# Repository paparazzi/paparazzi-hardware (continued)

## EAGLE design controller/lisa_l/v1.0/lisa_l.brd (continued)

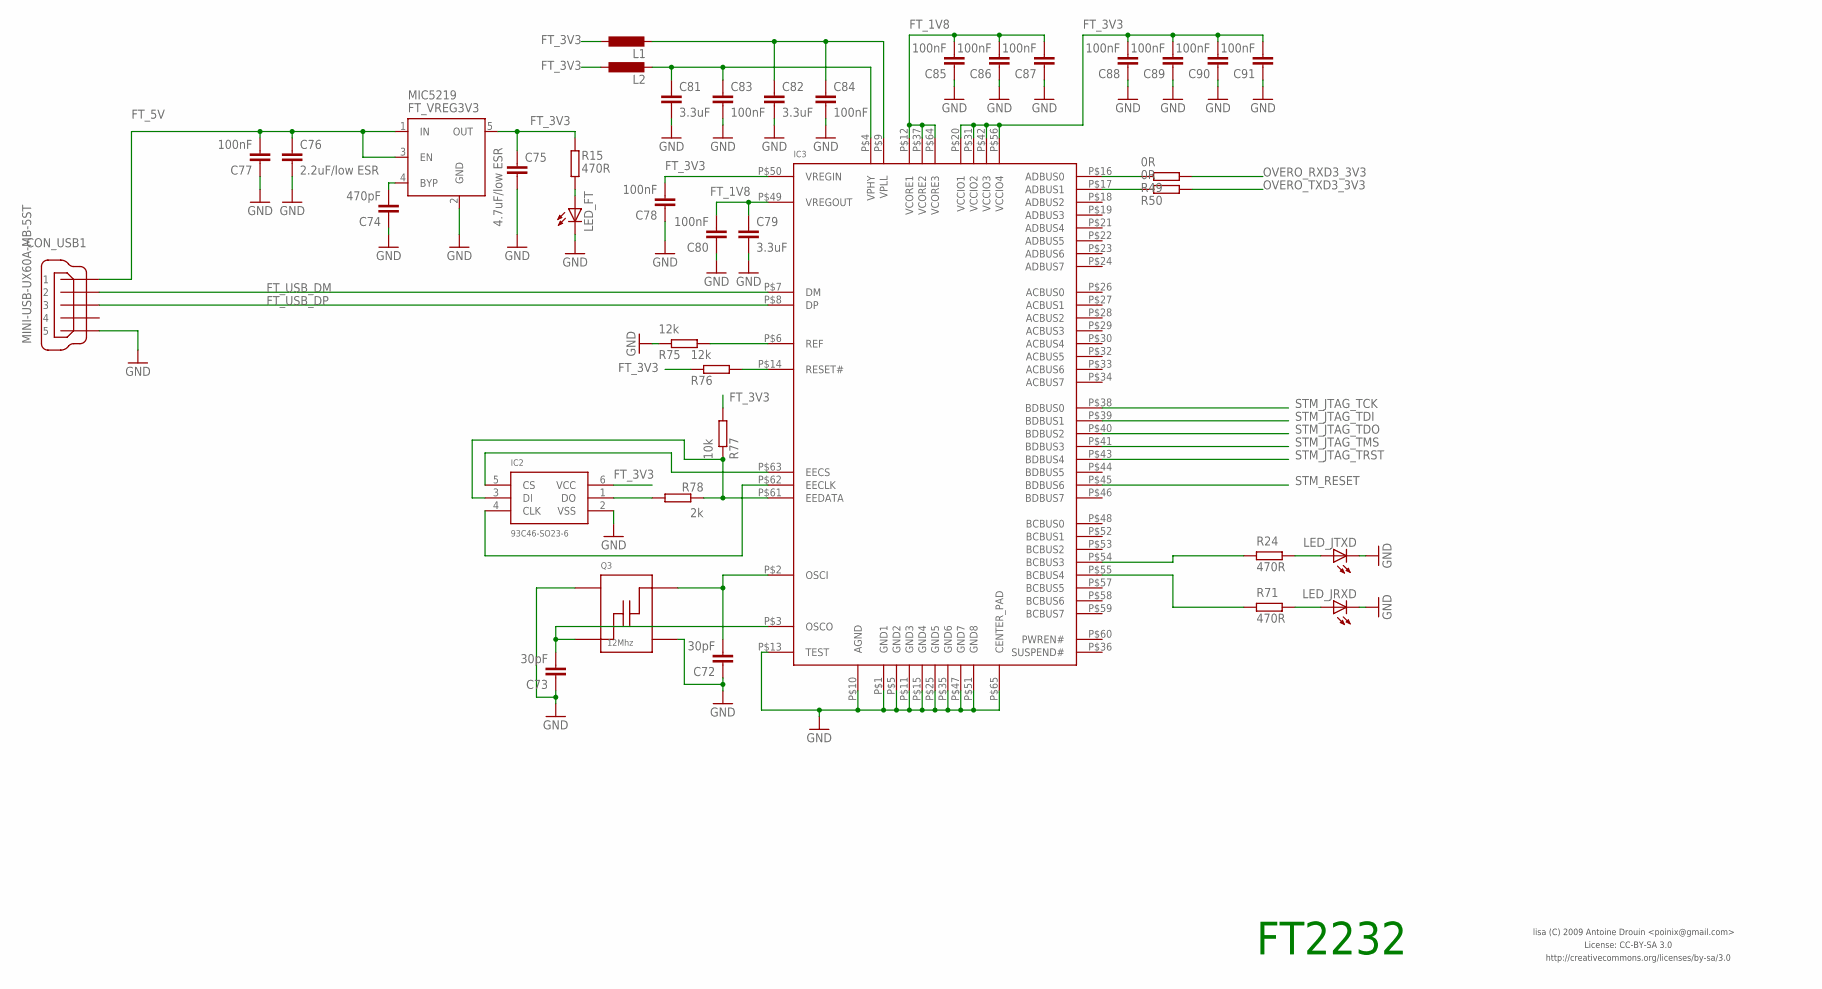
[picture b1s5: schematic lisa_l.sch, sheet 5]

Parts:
C72, C73: 30pF; 0603-CAP
C74: 470pF; 0603-CAP
C75: 4.7uF/low ESR; 0603-CAP
C76: 2.2uF/low ESR; 0603-CAP
C77, C78, C80, C83, C84, C85, C86, C87, C88, C89, C90, C91: 100nF; 0603-CAP
C79, C81, C82: 3.3uF; 0603-CAP
CON_USB1: MINI-USB-UX60A-MB-5ST; UX60A-MB-5ST
FT_VREG3V3: MIC5219; SOT23-5
IC2: 93C46-SO23-6; SO23-6
IC3: FT2232HQ; QFN64
L1, L2: INDUCTOR-0603; 0603-IND
LED_FT: LED-0603; 0603-LED
LED_JRXD: LED-0603; 0603-LED
LED_JTXD: LED-0603; 0603-LED
Q3: 12Mhz; ABM8
R15, R24, R71: 470R; 0603-RES
R49, R50: 0R; 0603-RES
R75, R76: 12k; 0603-RES
R77: 10k; 0603-RES
R78: 2k; 0603-RES

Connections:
FT_1V8: C79.P$1 (1), C80.P$2 (2), C85.P$2 (2), C86.P$2 (2), C87.P$2 (2), IC3.P$12 (VCORE1), IC3.P$37 (VCORE2), IC3.P$49 (VREGOUT), IC3.P$64 (VCORE3)
FT_3V3: C75.P$1 (1), C78.P$2 (2), C88.P$2 (2), C89.P$2 (2), C90.P$2 (2), C91.P$2 (2), FT_VREG3V3.5 (OUT), IC2.6 (VCC), IC3.P$20 (VCCIO1), IC3.P$31 (VCCIO2), IC3.P$42 (VCCIO3), IC3.P$50 (VREGIN), IC3.P$56 (VCCIO4), L1.P$1 (1), L2.P$1 (1), R15.P$2 (2), R76.P$1 (1), R77.P$2 (2)
FT_5V: C76.P$1 (1), C77.P$2 (2), CON_USB1.1, FT_VREG3V3.1 (IN), FT_VREG3V3.3 (EN)
FT_USB_DM: CON_USB1.2, IC3.P$7 (DM)
FT_USB_DP: CON_USB1.3, IC3.P$8 (DP)
GND: C72.P$1 (1), C73.P$1 (1), C74.P$1 (1), C75.P$2 (2), C76.P$2 (2), C77.P$1 (1), C78.P$1 (1), C79.P$2 (2), C80.P$1 (1), C81.P$2 (2), C82.P$2 (2), C83.P$2 (2), C84.P$2 (2), C85.P$1 (1), C86.P$1 (1), C87.P$1 (1), C88.P$1 (1), C89.P$1 (1), C90.P$1 (1), C91.P$1 (1), CON_USB1.5, FT_VREG3V3.2 (GND), IC2.2 (VSS), IC3.P$1 (GND1), IC3.P$5 (GND2), IC3.P$10 (AGND), IC3.P$11 (GND3), IC3.P$13 (TEST), IC3.P$15 (GND4), IC3.P$25 (GND5), IC3.P$35 (GND6), IC3.P$47 (GND7), IC3.P$51 (GND8), IC3.P$65 (CENTER_PAD), LED_FT.C, LED_JRXD.C, LED_JTXD.C, Q3.P$2, Q3.P$4, R75.P$1 (1); also elsewhere on the board
unnamed: LED_JTXD.A, R24.P$1 (1)
unnamed: IC3.P$16 (ADBUS0), R49.P$1 (1)
unnamed: IC3.P$54 (BCBUS3), R24.P$2 (2)
unnamed: LED_JRXD.A, R71.P$1 (1)
unnamed: IC3.P$55 (BCBUS4), R71.P$2 (2)
unnamed: LED_FT.A, R15.P$1 (1)
unnamed: IC3.P$17 (ADBUS1), R50.P$1 (1)
unnamed: C72.P$2 (2), IC3.P$2 (OSCI), Q3.P$3
unnamed: C73.P$2 (2), IC3.P$3 (OSCO), Q3.P$1
unnamed: IC3.P$6 (REF), R75.P$2 (2)
unnamed: IC3.P$14 (RESET#), R76.P$2 (2)
unnamed: C74.P$2 (2), FT_VREG3V3.4 (BYP)
unnamed: C81.P$1 (1), C83.P$1 (1), IC3.P$4 (VPHY), L2.P$2 (2)
unnamed: C82.P$1 (1), C84.P$1 (1), IC3.P$9 (VPLL), L1.P$2 (2)
unnamed: IC2.4 (CLK), IC3.P$62 (EECLK)
unnamed: IC2.5 (CS), IC3.P$63 (EECS)
unnamed: IC2.3 (DI), IC3.P$61 (EEDATA), R77.P$1 (1), R78.P$1 (1)
unnamed: IC2.1 (DO), R78.P$2 (2)
OVERO_RXD3_3V3: R49.P$2 (2); also elsewhere on the board
OVERO_TXD3_3V3: R50.P$2 (2); also elsewhere on the board
STM_JTAG_TCK: IC3.P$38 (BDBUS0); also elsewhere on the board
STM_JTAG_TDI: IC3.P$39 (BDBUS1); also elsewhere on the board
STM_JTAG_TDO: IC3.P$40 (BDBUS2); also elsewhere on the board
STM_JTAG_TMS: IC3.P$41 (BDBUS3); also elsewhere on the board
STM_JTAG_TRST: IC3.P$43 (BDBUS4); also elsewhere on the board
STM_RESET: IC3.P$45 (BDBUS6); also elsewhere on the board

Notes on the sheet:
FT2232
License: CC-BY-SA 3.0
http://creativecommons.org/licenses/by-sa/3.0
lisa (C) 2009 Antoine Drouin <poinix@gmail.com>

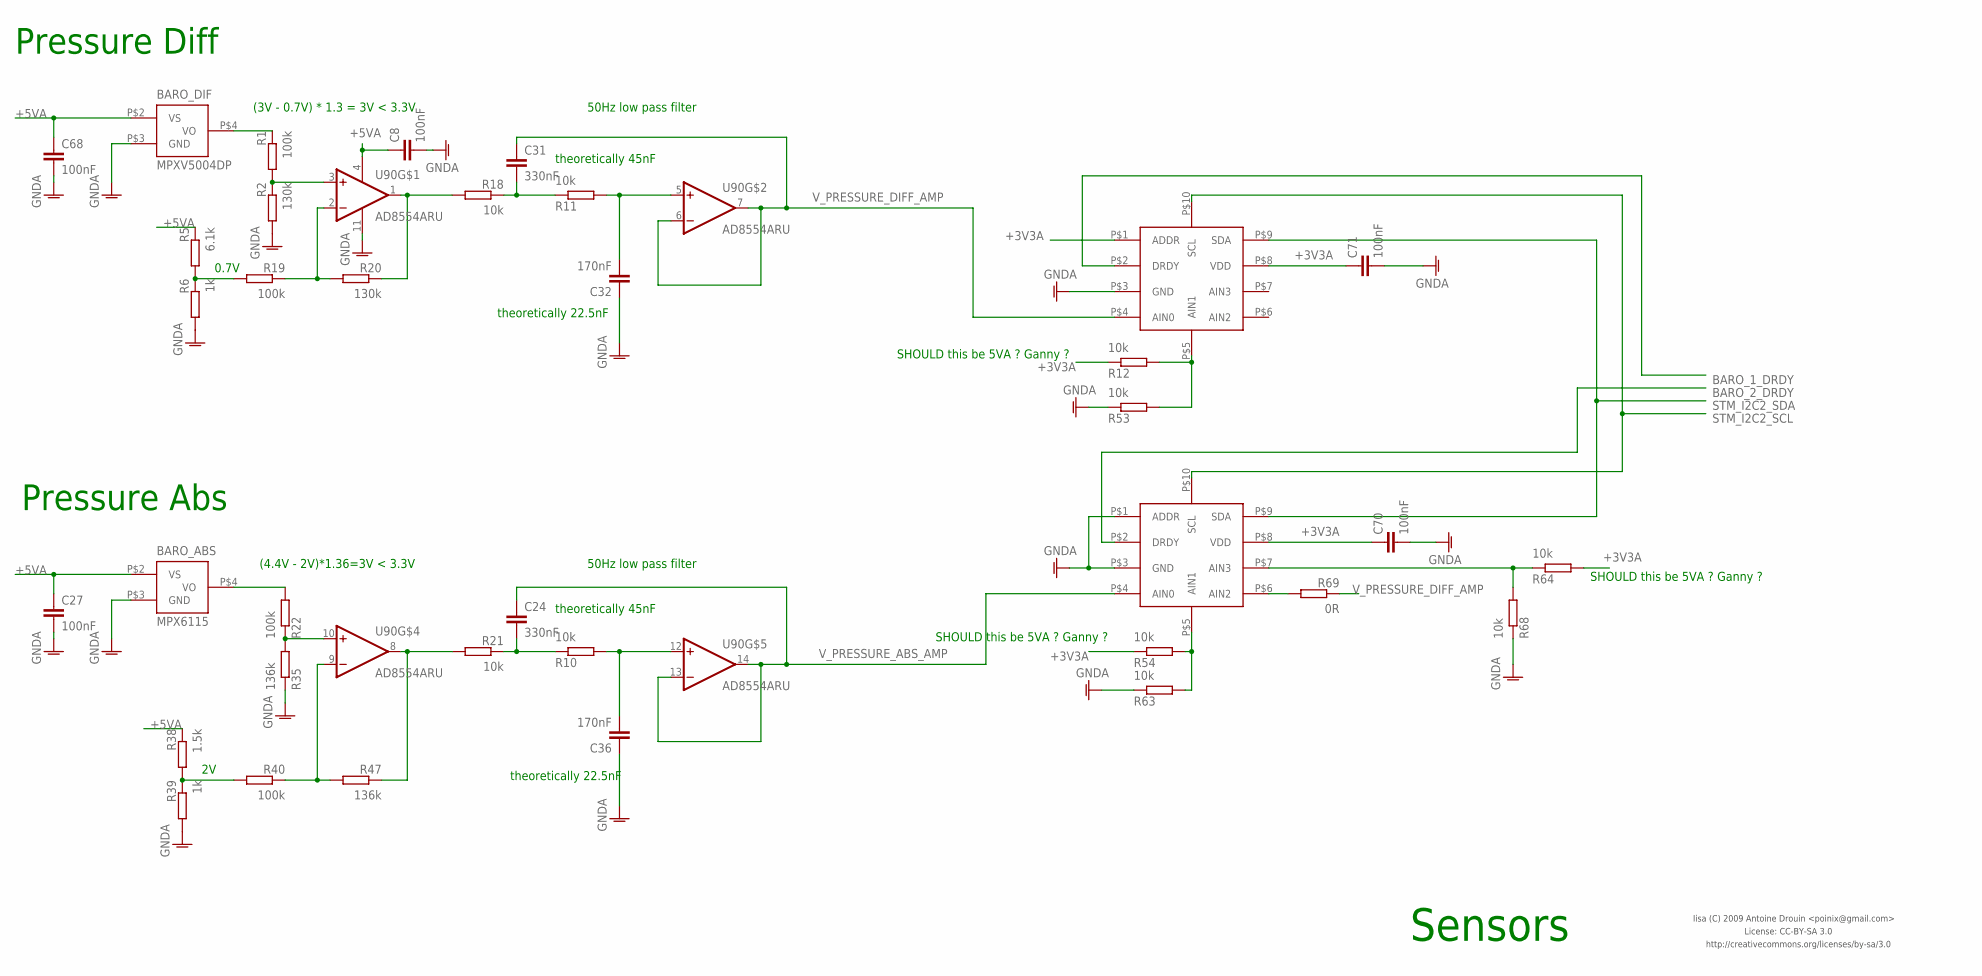
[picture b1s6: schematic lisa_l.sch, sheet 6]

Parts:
ADC1, ADC2: ADS1114; R-PQFP-N10
BARO_ABS: MPX6115; CASE_1317
BARO_DIF: MPXV5004DP; CASE1351
C8, C27, C68, C70, C71: 100nF; 0603-CAP
C24, C31: 330nF; 0603-CAP
C32, C36: 170nF; 0603-CAP
R1, R19, R22, R40: 100k; 0603-RES
R2, R20: 130k; 0603-RES
R5: 6.1k; 0603-RES
R6, R39: 1k; 0603-RES
R10, R11, R12, R18, R21, R53, R54, R63, R64, R68: 10k; 0603-RES
R35, R47: 136k; 0603-RES
R38: 1.5k; 0603-RES
R69: 0R; 0603-RES
U90: AD8554ARU; TSSOP14

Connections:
+3V3A: ADC1.P$1 (ADDR), ADC1.P$8 (VDD), ADC2.P$8 (VDD), C70.P$1 (1), C71.P$1 (1), R12.P$1 (1), R54.P$1 (1), R64.P$2 (2); also elsewhere on the board
+5VA: BARO_ABS.P$2 (VS), BARO_DIF.P$2 (VS), C8.P$1 (1), C27.P$1 (1), C68.P$1 (1), R5.P$1 (1), R38.P$1 (1), U90.4 (V+); also elsewhere on the board
BARO_1_DRDY: ADC1.P$2 (DRDY); also elsewhere on the board
BARO_2_DRDY: ADC2.P$2 (DRDY); also elsewhere on the board
GNDA: ADC1.P$3 (GND), ADC2.P$1 (ADDR), ADC2.P$3 (GND), BARO_ABS.P$3 (GND), BARO_DIF.P$3 (GND), C8.P$2 (2), C27.P$2 (2), C32.P$1 (1), C36.P$1 (1), C68.P$2 (2), C70.P$2 (2), C71.P$2 (2), R2.P$2 (2), R6.P$2 (2), R35.P$1 (1), R39.P$2 (2), R53.P$1 (1), R63.P$1 (1), R68.P$1 (1), U90.11 (V-); also elsewhere on the board
unnamed: ADC1.P$5 (AIN1), R12.P$2 (2), R53.P$2 (2)
unnamed: C36.P$2 (2), R10.P$2 (2), U90.12 (+IN)
unnamed: ADC2.P$5 (AIN1), R54.P$2 (2), R63.P$2 (2)
unnamed: BARO_ABS.P$4 (VO), R22.P$2 (2)
unnamed: R1.P$2 (2), R2.P$1 (1), U90.3 (+IN)
unnamed: BARO_DIF.P$4 (VO), R1.P$1 (1)
unnamed: ADC2.P$6 (AIN2), R69.P$2 (2)
unnamed: ADC2.P$7 (AIN3), R64.P$1 (1), R68.P$2 (2)
unnamed: C32.P$2 (2), R11.P$2 (2), U90.5 (+IN)
unnamed: R5.P$2 (2), R6.P$1 (1), R19.P$2 (2)
unnamed: C31.P$2 (2), R11.P$1 (1), R18.P$1 (1)
unnamed: R18.P$2 (2), R20.P$1 (1), U90.1 (OUT)
unnamed: R19.P$1 (1), R20.P$2 (2), U90.2 (-IN)
unnamed: R22.P$1 (1), R35.P$2 (2), U90.10 (+IN)
unnamed: R21.P$2 (2), R47.P$1 (1), U90.8 (OUT)
unnamed: C24.P$2 (2), R10.P$1 (1), R21.P$1 (1)
unnamed: R38.P$2 (2), R39.P$1 (1), R40.P$2 (2)
unnamed: R40.P$1 (1), R47.P$2 (2), U90.9 (-IN)
STM_I2C2_SCL: ADC1.P$10 (SCL), ADC2.P$10 (SCL); also elsewhere on the board
STM_I2C2_SDA: ADC1.P$9 (SDA), ADC2.P$9 (SDA); also elsewhere on the board
V_PRESSURE_ABS_AMP: ADC2.P$4 (AIN0), C24.P$1 (1), U90.13 (-IN), U90.14 (OUT)
V_PRESSURE_DIFF_AMP: ADC1.P$4 (AIN0), C31.P$1 (1), R69.P$1 (1), U90.6 (-IN), U90.7 (OUT)

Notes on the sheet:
Pressure Abs
Sensors
Pressure Diff
License: CC-BY-SA 3.0
http://creativecommons.org/licenses/by-sa/3.0
lisa (C) 2009 Antoine Drouin <poinix@gmail.com>
(4.4V - 2V)*1.36=3V < 3.3V
(3V - 0.7V) * 1.3 = 3V < 3.3V
50Hz low pass filter
0.7V
theoretically 45nF
theoretically 22.5nF
SHOULD this be 5VA ? Ganny ?

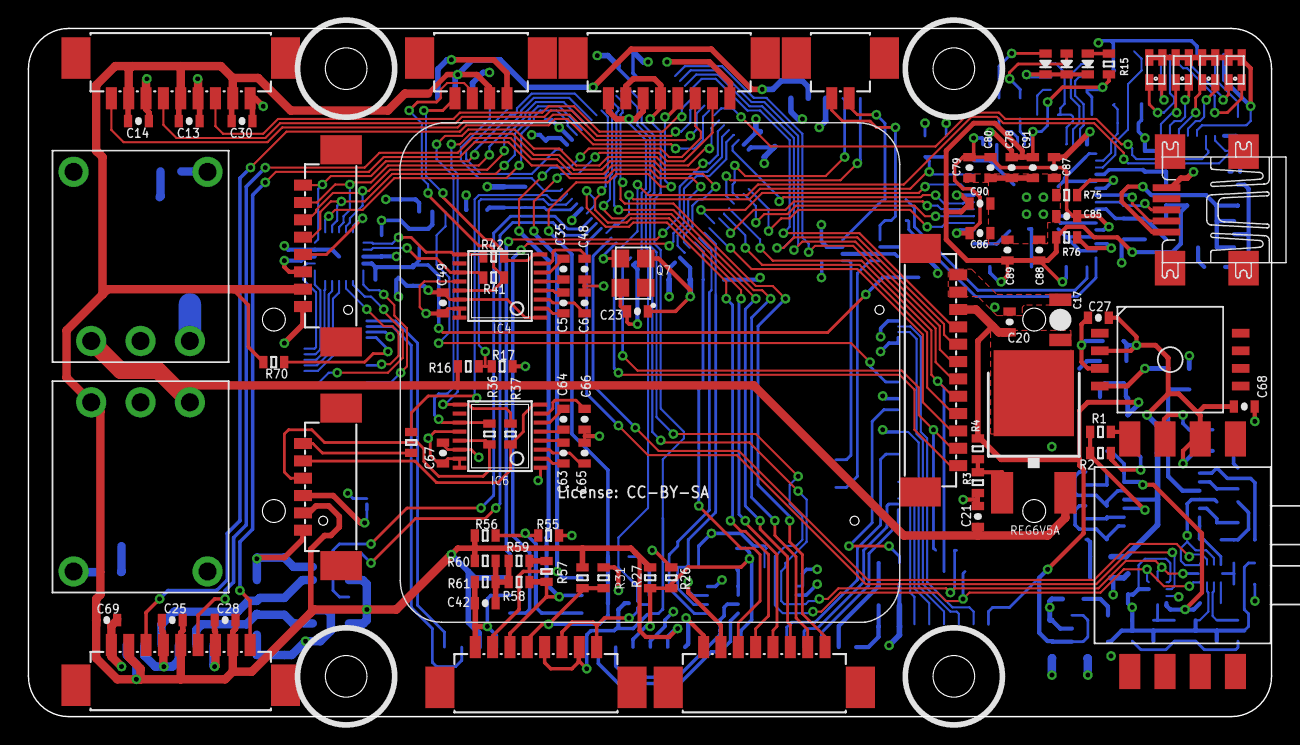
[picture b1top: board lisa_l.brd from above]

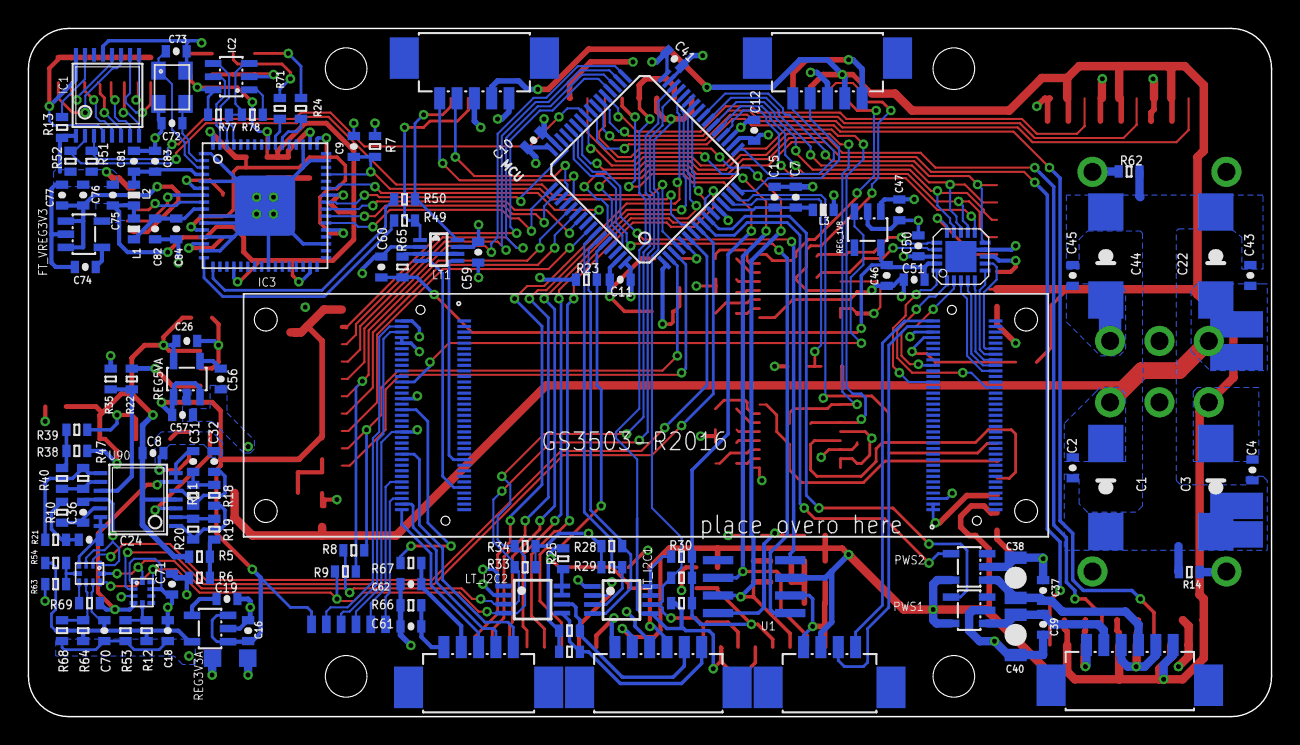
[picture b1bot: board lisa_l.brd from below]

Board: 4 copper layers, 89.6 x 49.6 mm, 224 parts (139 on the bottom side), 181 nets.

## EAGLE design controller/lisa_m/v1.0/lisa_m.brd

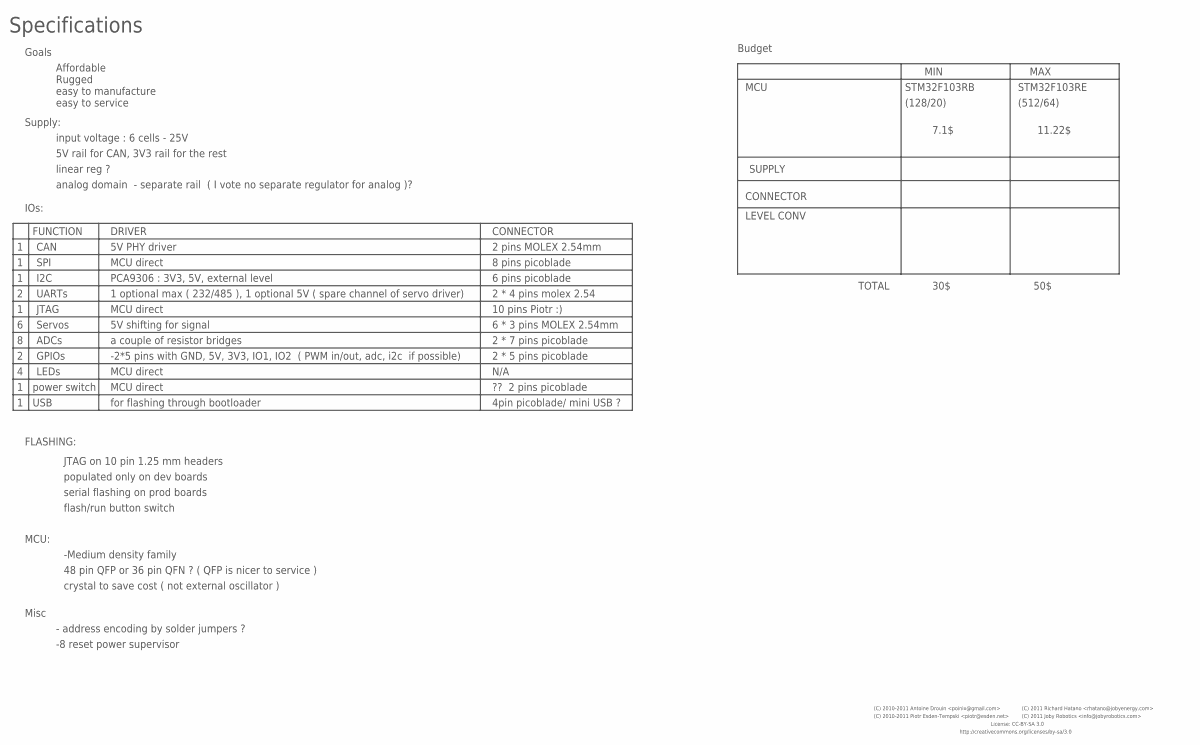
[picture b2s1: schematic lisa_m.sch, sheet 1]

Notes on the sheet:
Specifications
input voltage : 6 cells - 25V
IOs:
CAN
SPI
I2C
UARTs
Servos
1 optional max ( 232/485 ), 1 optional 5V ( spare channel of servo driver)
5V shifting for signal
FLASHING:
JTAG on 10 pin 1.25 mm headers
populated only on dev boards
serial flashing on prod boards
flash/run button switch
PCA9306 : 3V3, 5V, external level
MCU:
-Medium density family
48 pin QFP or 36 pin QFN ? ( QFP is nicer to service )
crystal to save cost ( not external oscillator )
Supply:
5V rail for CAN, 3V3 rail for the rest
linear reg ?
analog domain - separate rail ( I vote no separate regulator for analog )?
Goals
Affordable
Rugged
easy to manufacture
easy to service
Misc
- address encoding by solder jumpers ?
JTAG
ADCs
-2*5 pins with GND, 5V, 3V3, IO1, IO2 ( PWM in/out, adc, i2c if possible)
LEDs
5V PHY driver
power switch
MCU direct
a couple of resistor bridges
-8 reset power supervisor

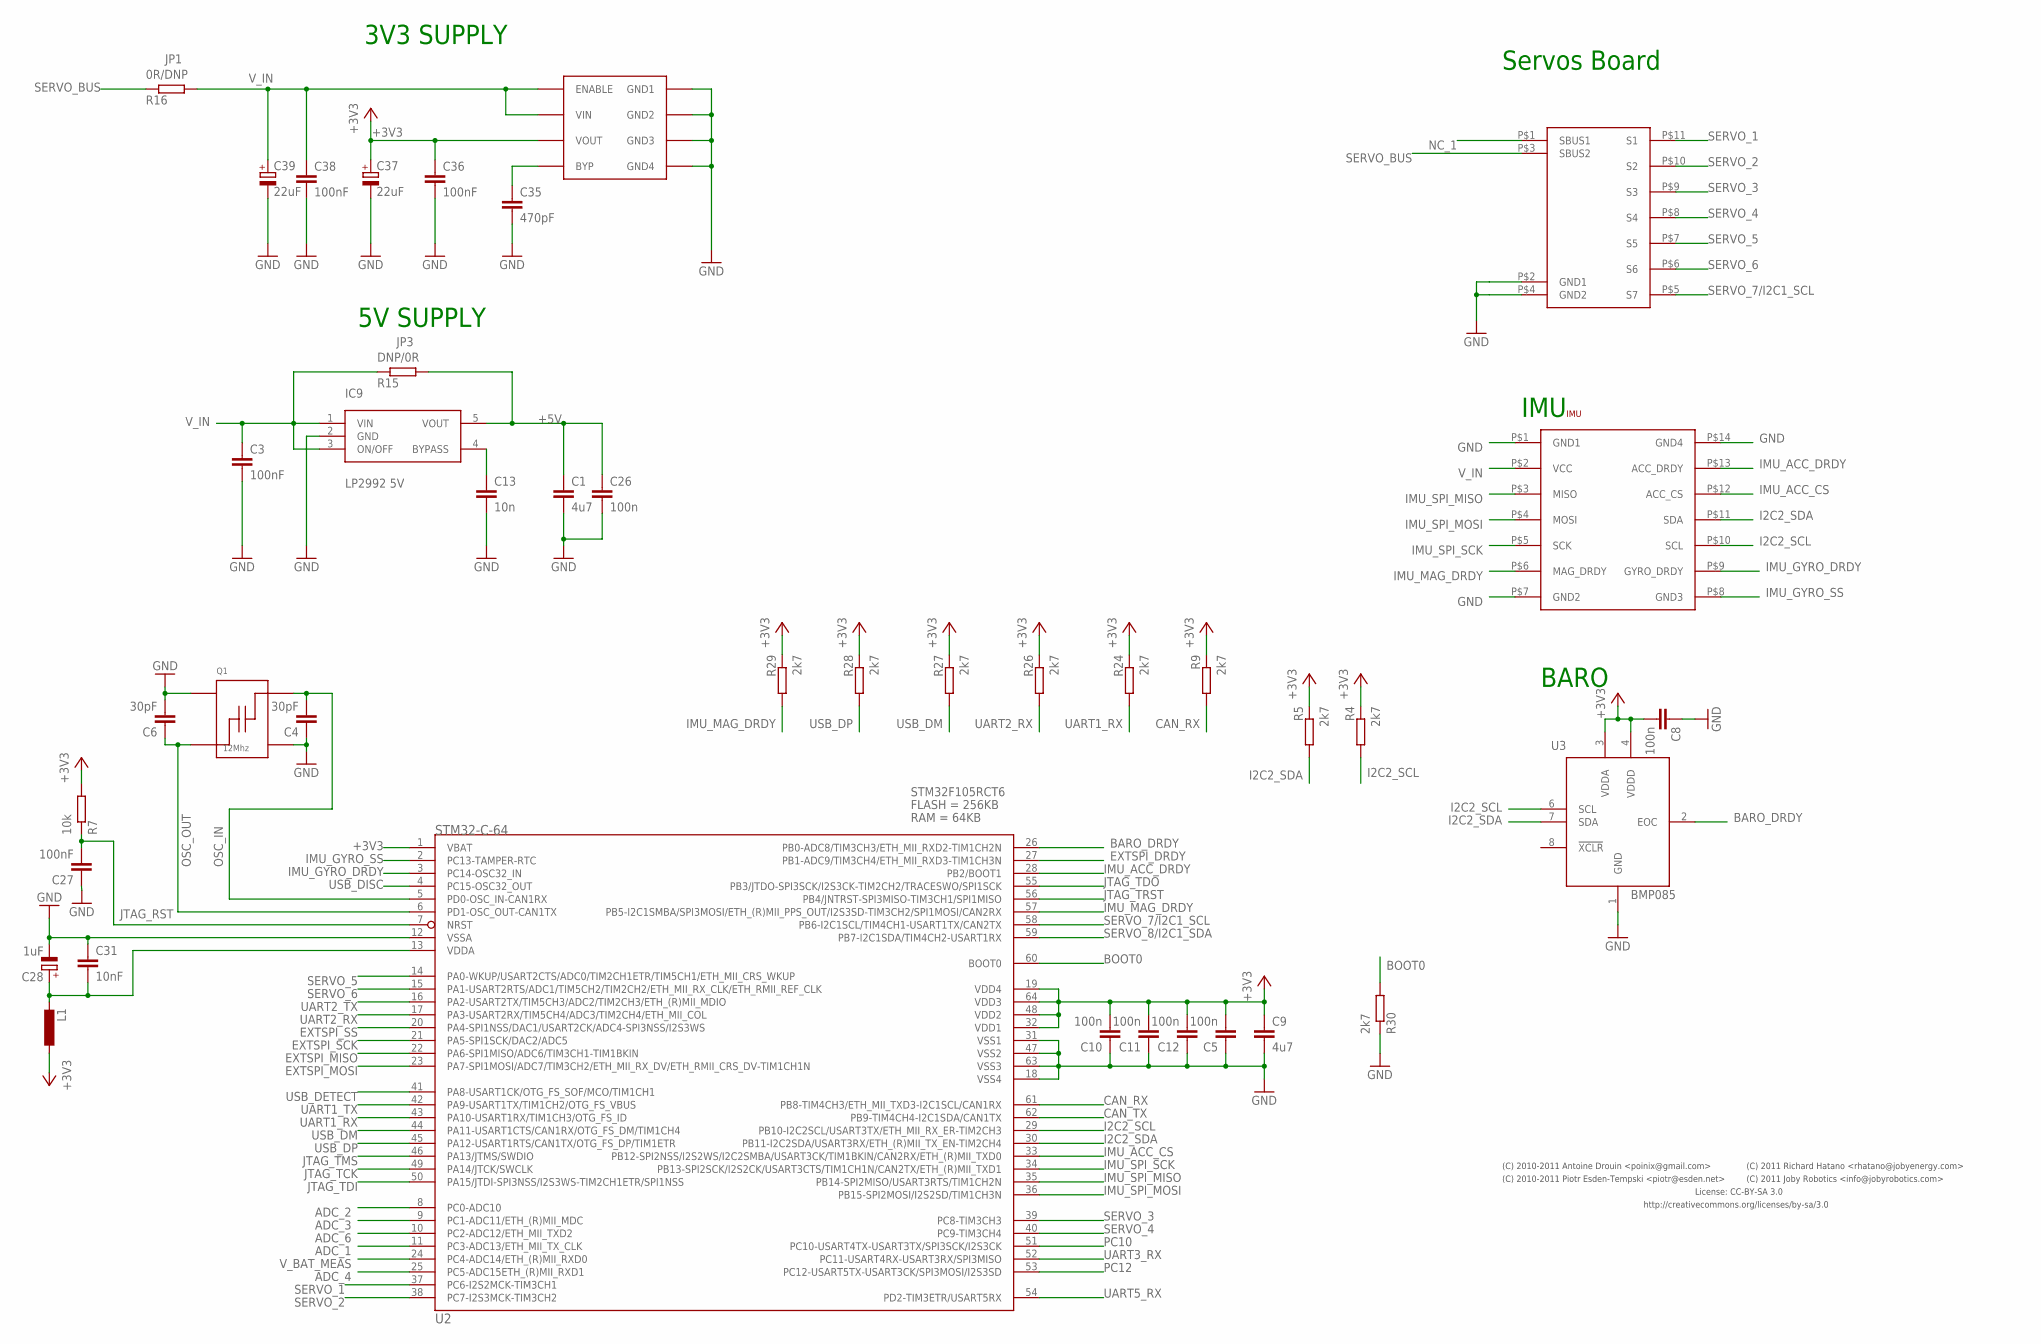
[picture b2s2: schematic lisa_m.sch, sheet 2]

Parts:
C1, C9: 4u7; 0805-CAP
C3, C36: 100nF; 0603-CAP
C4, C6: 30pF; 0402-CAP
C5, C8, C10, C11, C12: 100n; 0402-CAP
C13: 10n; 0402-CAP
C26: 100n; 0603-CAP
C27, C38: 100nF; 0402-CAP
C28: 1uF; 0603-POL-CAP
C31: 10nF; 0402-CAP
C35: 470pF; 0402-CAP
C37, C39: 22uF; 3528/B
IC9: LP2992 5V; SOT23-5
IMU: ASPIRIN; ASPIRIN_1
L1: INDUCTOR-0603; 0603-IND
Q1: 12Mhz; ABM8
R4, R5, R9, R24, R26, R27, R28, R29, R30: 2k7; 0402-RES
R7: 10k; 0402-RES
R15: DNP/0R; 0402-RES
R16: 0R/DNP; 0402-RES
U2: STM32-C-64; LQFP64; PART_NR STM32F105RCT6
U3: BMP085; LCC8
U$1: LISA_M_VBOARD
VREG1: MIC5209; SOIC8

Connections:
+3V3: C5.P$2 (2), C8.P$2 (2), C9.P$1 (1), C10.P$2 (2), C11.P$2 (2), C12.P$2 (2), C36.P$1 (1), C37.+, L1.P$1 (1), R4.P$1 (1), R5.P$1 (1), R7.P$2 (2), R9.P$1 (1), R24.P$1 (1), R26.P$1 (1), R27.P$1 (1), R28.P$1 (1), R29.P$1 (1), U2.1 (VBAT), U2.19 (VDD4), U2.32 (VDD1), U2.48 (VDD2), U2.64 (VDD3), U3.3 (VDDA), U3.4 (VDDD), VREG1.3 (VOUT); also elsewhere on the board
+5V: C1.P$1 (1), C26.P$1 (1), IC9.5 (VOUT), R15.P$2 (2); also elsewhere on the board
ADC_1: U2.11 (PC3-ADC13/ETH_MII_TX_CLK); also elsewhere on the board
ADC_2: U2.8 (PC0-ADC10); also elsewhere on the board
ADC_3: U2.9 (PC1-ADC11/ETH_(R)MII_MDC); also elsewhere on the board
ADC_4: U2.25 (PC5-ADC15ETH_(R)MII_RXD1); also elsewhere on the board
ADC_6: U2.10 (PC2-ADC12/ETH_MII_TXD2); also elsewhere on the board
BARO_DRDY: U2.26 (PB0-ADC8/TIM3CH3/ETH_MII_RXD2-TIM1CH2N), U3.2 (EOC)
BOOT0: R30.P$2 (2), U2.60 (BOOT0); also elsewhere on the board
CAN_RX: R9.P$2 (2), U2.61 (PB8-TIM4CH3/ETH_MII_TXD3-I2C1SCL/CAN1RX); also elsewhere on the board
CAN_TX: U2.62 (PB9-TIM4CH4-I2C1SDA/CAN1TX); also elsewhere on the board
EXTSPI_DRDY: U2.27 (PB1-ADC9/TIM3CH4/ETH_MII_RXD3-TIM1CH3N); also elsewhere on the board
EXTSPI_MISO: U2.22 (PA6-SPI1MISO/ADC6/TIM3CH1-TIM1BKIN); also elsewhere on the board
EXTSPI_MOSI: U2.23 (PA7-SPI1MOSI/ADC7/TIM3CH2/ETH_MII_RX_DV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); also elsewhere on the board
EXTSPI_SCK: U2.21 (PA5-SPI1SCK/DAC2/ADC5); also elsewhere on the board
EXTSPI_SS: U2.20 (PA4-SPI1NSS/DAC1/USART2CK/ADC4-SPI3NSS/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); also elsewhere on the board
GND: C1.P$2 (2), C3.P$2 (2), C4.P$1 (1), C5.P$1 (1), C6.P$2 (2), C8.P$1 (1), C9.P$2 (2), C10.P$1 (1), C11.P$1 (1), C12.P$1 (1), C13.P$2 (2), C26.P$2 (2), C27.P$1 (1), C28.-, C31.P$1 (1), C35.P$2 (2), C36.P$2 (2), C37.-, C38.P$2 (2), C39.-, IC9.2 (GND), IMU.P$1 (GND1), IMU.P$7 (GND2), IMU.P$14 (GND4), Q1.P$2, Q1.P$4, R30.P$1 (1), U2.12 (VSSA), U2.18 (VSS4), U2.31 (VSS1), U2.47 (VSS2), U2.63 (VSS3), U3.1 (GND), U$1.P$2 (GND1), U$1.P$4 (GND2), VREG1.5 (GND4), VREG1.6 (GND3), VREG1.7 (GND2), VREG1.8 (GND1); also elsewhere on the board
I2C2_SCL: IMU.P$10 (SCL), R4.P$2 (2), U2.29 (PB10-I2C2SCL/USART3TX/ETH_MII_RX_ER-TIM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), U3.6 (SCL); also elsewhere on the board
I2C2_SDA: IMU.P$11 (SDA), R5.P$2 (2), U2.30 (PB11-I2C2SDA/USART3RX/ETH_(R)MII_TX_EN-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), U3.7 (SDA); also elsewhere on the board
IMU_ACC_CS: IMU.P$12 (ACC_CS), U2.33 (PB12-SPI2NSS/I2S2WS/I2C2SMBA/USART3CK/T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)
IMU_ACC_DRDY: IMU.P$13 (ACC_DRDY), U2.28 (PB2/BOOT1)
IMU_GYRO_DRDY: IMU.P$9 (GYRO_DRDY), U2.3 (PC14-OSC32_IN)
IMU_GYRO_SS: IMU.P$8 (GND3), U2.2 (PC13-TAMPER-RTC)
IMU_MAG_DRDY: IMU.P$6 (MAG_DRDY), R29.P$2 (2), U2.57 (PB5-I2C1SMBA/SPI3MOSI/ETH_(R)MII_PPS_OU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)
IMU_SPI_MISO: IMU.P$3 (MISO), U2.35 (PB14-SPI2MISO/USART3RTS/TIM1CH2N)
IMU_SPI_MOSI: IMU.P$4 (MOSI), U2.36 (PB15-SPI2MOSI/I2S2SD/TIM1CH3N)
IMU_SPI_SCK: IMU.P$5 (SCK), U2.34 (PB13-SPI2SCK/I2S2CK/USART3CTS/TIM1CH1N/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)
JTAG_RST: C27.P$2 (2), R7.P$1 (1), U2.7 (NRST); also elsewhere on the board
JTAG_TCK: U2.49 (PA14/JTCK/SWCLK); also elsewhere on the board
JTAG_TDI: U2.50 (PA15/JTDI-SPI3NSS/I2S3WS-TIM2CH1ETR/SPI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); also elsewhere on the board
JTAG_TDO: U2.55 (PB3/JTDO-SPI3SCK/I2S3CK-TIM2CH2/TRACESW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); also elsewhere on the board
JTAG_TMS: U2.46 (PA13/JTMS/SWDIO); also elsewhere on the board
JTAG_TRST: U2.56 (PB4/JNTRST-SPI3MISO-TIM3CH1/SPI1MISO); also elsewhere on the board
unnamed: C13.P$1 (1), IC9.4 (BYPASS)
unnamed: C35.P$1 (1), VREG1.4 (BYP)
NC_1: U$1.P$1 (SBUS1)
OSC_IN: C4.P$2 (2), Q1.P$3, U2.5 (PD0-OSC_IN-CAN1RX)
OSC_OUT: C6.P$1 (1), Q1.P$1, U2.6 (PD1-OSC_OUT-CAN1TX)
PC10: U2.51 (PC10-USART4TX-USART3TX/SPI3SCK/I2S3CK); also elsewhere on the board
PC12: U2.53 (PC12-USART5TX-USART3CK/SPI3MOSI/I2S3SD); also elsewhere on the board
SERVO_1: U2.37 (PC6-I2S2MCK-TIM3CH1), U$1.P$11 (S1)
SERVO_2: U2.38 (PC7-I2S3MCK-TIM3CH2), U$1.P$10 (S2)
SERVO_3: U2.39 (PC8-TIM3CH3), U$1.P$9 (S3)
SERVO_4: U2.40 (PC9-TIM3CH4), U$1.P$8 (S4)
SERVO_5: U2.14 (PA0-WKUP/USART2CTS/ADC0/TIM2CH1ETR/TIM5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), U$1.P$7 (S5)
SERVO_6: U2.15 (PA1-USART2RTS/ADC1/TIM5CH2/TIM2CH2/ETH_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), U$1.P$6 (S6)
SERVO_7/I2C1_SCL: U2.58 (PB6-I2C1SCL/TIM4CH1-USART1TX/CAN2TX), U$1.P$5 (S7); also elsewhere on the board
SERVO_8/I2C1_SDA: U2.59 (PB7-I2C1SDA/TIM4CH2-USART1RX); also elsewhere on the board
SERVO_BUS: R16.P$1 (1), U$1.P$3 (SBUS2)
UART1_RX: R24.P$2 (2), U2.43 (PA10-USART1RX/TIM1CH3/OTG_FS_ID); also elsewhere on the board
UART1_TX: U2.42 (PA9-USART1TX/TIM1CH2/OTG_FS_VBUS); also elsewhere on the board
UART2_RX: R26.P$2 (2), U2.17 (PA3-USART2RX/TIM5CH4/ADC3/TIM2CH4/ETH_M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); also elsewhere on the board
UART2_TX: U2.16 (PA2-USART2TX/TIM5CH3/ADC2/TIM2CH3/ETH_(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); also elsewhere on the board
UART3_RX: U2.52 (PC11-USART4RX-USART3RX/SPI3MISO); also elsewhere on the board
UART5_RX: U2.54 (PD2-TIM3ETR/USART5RX); also elsewhere on the board
USB_DETECT: U2.41 (PA8-USART1CK/OTG_FS_SOF/MCO/TIM1CH1); also elsewhere on the board
USB_DISC: U2.4 (PC15-OSC32_OUT); also elsewhere on the board
USB_DM: R27.P$2 (2), U2.44 (PA11-USART1CTS/CAN1RX/OTG_FS_DM/TIM1CH4); also elsewhere on the board
USB_DP: R28.P$2 (2), U2.45 (PA12-USART1RTS/CAN1TX/OTG_FS_DP/TIM1ETR); also elsewhere on the board
VDDA: C28.+, C31.P$2 (2), L1.P$2 (2), U2.13 (VDDA)
V_BAT_MEAS: U2.24 (PC4-ADC14/ETH_(R)MII_RXD0); also elsewhere on the board
V_IN: C3.P$1 (1), C38.P$1 (1), C39.+, IC9.1 (VIN), IC9.3 (ON/OFF), IMU.P$2 (VCC), R15.P$1 (1), R16.P$2 (2), VREG1.1 (ENABLE), VREG1.2 (VIN); also elsewhere on the board

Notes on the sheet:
Servos Board
IMU
BARO
3V3 SUPPLY
5V SUPPLY
JP3
JP1
License: CC-BY-SA 3.0
http://creativecommons.org/licenses/by-sa/3.0
(C) 2010-2011 Piotr Esden-Tempski <piotr@esden.net>
(C) 2010-2011 Antoine Drouin <poinix@gmail.com>
(C) 2011 Richard Hatano <rhatano@jobyenergy.com>
(C) 2011 Joby Robotics <info@jobyrobotics.com>

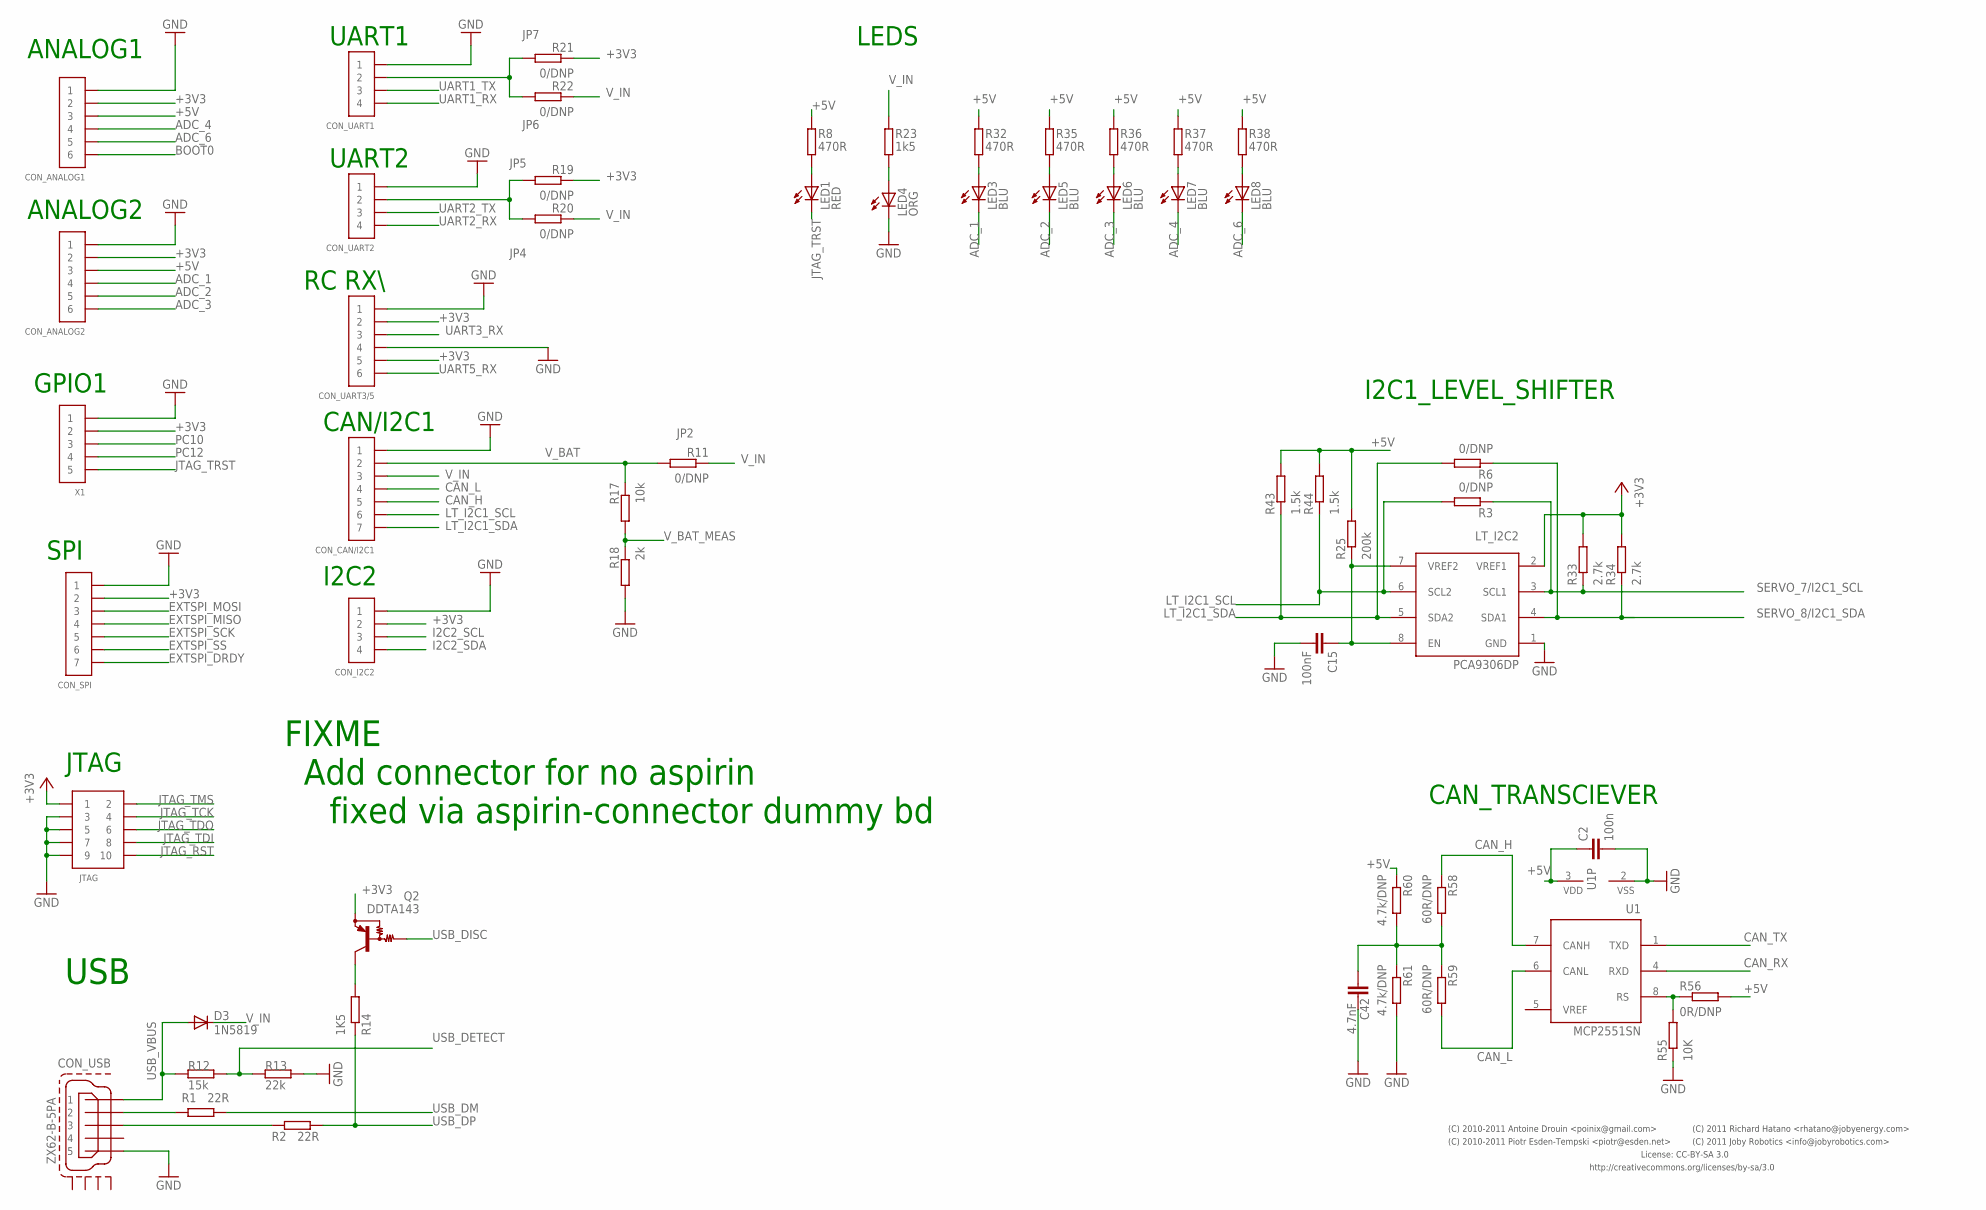
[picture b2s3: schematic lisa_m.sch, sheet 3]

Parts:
C2: 100n; 0402-CAP
C15: 100nF; 0402-CAP
C42: 4.7nF; 0603-CAP
CON_ANALOG1, CON_ANALOG2: CONN_6-1-53398; PB-53398-06
CON_CAN/I2C1: CONN_7-1-53261; PB-53261-07
CON_I2C2: CONN_4-1-53398; PB-53398-04
CON_SPI: CONN_7-1-53398; PB-53398-07
CON_UART1, CON_UART2: CONN_4-1-53398; PB-53398-04
CON_UART3/5: CONN_6-1PB-53398-06_SMALL; PB-53398-06
CON_USB: ZX62-B-5PA
D3: 1N5819; MICROMELF-R
JTAG: PIN_HDR_EDG_1.27MM_5-2; FTSH-105-DV
LED1: RED; 0402-LED
LED3, LED5, LED6, LED7, LED8: BLU; 0402-LED
LED4: ORG; 0402-LED
LT_I2C2: PCA9306DP; TSSOP_B3
Q2: DDTA143; SOT23
R1, R2: 22R; 0402-RES
R3, R6: 0/DNP; 0603-RES
R8, R32, R35, R36, R37, R38: 470R; 0402-RES
R11, R19, R20, R21, R22: 0/DNP; 0402-RES
R12: 15k; 0402-RES
R13: 22k; 0402-RES
R14: 1K5; 0402-RES
R17: 10k; 0402-RES
R18: 2k; 0402-RES
R23: 1k5; 0402-RES
R25: 200k; 0402-RES
R33, R34: 2.7k; 0402-RES
R43, R44: 1.5k; 0402-RES
R55: 10K; 0402-RES
R56: 0R/DNP; 0402-RES
R58, R59: 60R/DNP; 0402-RES
R60, R61: 4.7k/DNP; 0402-RES
U1: MCP2551SN; SO-08
X1: CONN_5-1-53398; PB-53398-05

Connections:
+3V3: CON_ANALOG1.2, CON_ANALOG2.2, CON_I2C2.2, CON_SPI.2, CON_UART3/5.2, CON_UART3/5.5, JTAG.1, LT_I2C2.2 (VREF1), Q2.2 (E), R19.P$1 (1), R21.P$1 (1), R33.P$2 (2), R34.P$2 (2), X1.2; also elsewhere on the board
+5V: C2.P$1 (1), CON_ANALOG1.3, CON_ANALOG2.3, R8.P$2 (2), R25.P$2 (2), R32.P$2 (2), R35.P$2 (2), R36.P$2 (2), R37.P$2 (2), R38.P$2 (2), R43.P$2 (2), R44.P$2 (2), R56.P$2 (2), R60.P$1 (1), U1.3 (VDD); also elsewhere on the board
ADC_1: CON_ANALOG2.4, LED3.C; also elsewhere on the board
ADC_2: CON_ANALOG2.5, LED5.C; also elsewhere on the board
ADC_3: CON_ANALOG2.6, LED6.C; also elsewhere on the board
ADC_4: CON_ANALOG1.4, LED7.C; also elsewhere on the board
ADC_6: CON_ANALOG1.5, LED8.C; also elsewhere on the board
BOOT0: CON_ANALOG1.6; also elsewhere on the board
CAN_CENTER: C42.P$2 (2), R58.P$2 (2), R59.P$1 (1), R60.P$2 (2), R61.P$1 (1)
CAN_H: CON_CAN/I2C1.5, R58.P$1 (1), U1.7 (CANH)
CAN_L: CON_CAN/I2C1.4, R59.P$2 (2), U1.6 (CANL)
CAN_RX: U1.4 (RXD); also elsewhere on the board
CAN_TX: U1.1 (TXD); also elsewhere on the board
EXTSPI_DRDY: CON_SPI.7; also elsewhere on the board
EXTSPI_MISO: CON_SPI.4; also elsewhere on the board
EXTSPI_MOSI: CON_SPI.3; also elsewhere on the board
EXTSPI_SCK: CON_SPI.5; also elsewhere on the board
EXTSPI_SS: CON_SPI.6; also elsewhere on the board
FT_USB_DM: CON_USB.PIN_2 (2), R1.P$1 (1)
FT_USB_DP: CON_USB.PIN_3 (3), R2.P$1 (1)
GND: C2.P$2 (2), C15.P$2 (2), C42.P$1 (1), CON_ANALOG1.1, CON_ANALOG2.1, CON_CAN/I2C1.1, CON_I2C2.1, CON_SPI.1, CON_UART1.1, CON_UART2.1, CON_UART3/5.1, CON_UART3/5.4, CON_USB.PIN_5 (5), JTAG.3, JTAG.5, JTAG.7, JTAG.9, LED4.C, LT_I2C2.1 (GND), R13.P$2 (2), R18.P$2 (2), R55.P$1 (1), R61.P$2 (2), U1.2 (VSS), X1.1; also elsewhere on the board
I2C2_SCL: CON_I2C2.3; also elsewhere on the board
I2C2_SDA: CON_I2C2.4; also elsewhere on the board
JTAG_RST: JTAG.10; also elsewhere on the board
JTAG_TCK: JTAG.4; also elsewhere on the board
JTAG_TDI: JTAG.8; also elsewhere on the board
JTAG_TDO: JTAG.6; also elsewhere on the board
JTAG_TMS: JTAG.2; also elsewhere on the board
JTAG_TRST: LED1.C, X1.5; also elsewhere on the board
LT_I2C1_SCL: CON_CAN/I2C1.6, LT_I2C2.6 (SCL2), R3.P$2 (2), R44.P$1 (1)
LT_I2C1_SDA: CON_CAN/I2C1.7, LT_I2C2.5 (SDA2), R6.P$2 (2), R43.P$1 (1)
unnamed: R55.P$2 (2), R56.P$1 (1), U1.8 (RS)
unnamed: CON_UART2.2, R19.P$2 (2), R20.P$2 (2)
unnamed: CON_UART1.2, R21.P$2 (2), R22.P$2 (2)
unnamed: LED3.A, R32.P$1 (1)
unnamed: C15.P$1 (1), LT_I2C2.7 (VREF2), LT_I2C2.8 (EN), R25.P$1 (1)
unnamed: LED5.A, R35.P$1 (1)
unnamed: LED1.A, R8.P$1 (1)
unnamed: LED6.A, R36.P$1 (1)
unnamed: LED4.A, R23.P$1 (1)
unnamed: Q2.3 (C), R14.P$2 (2)
unnamed: LED7.A, R37.P$1 (1)
unnamed: LED8.A, R38.P$1 (1)
PC10: X1.3; also elsewhere on the board
PC12: X1.4; also elsewhere on the board
SERVO_7/I2C1_SCL: LT_I2C2.3 (SCL1), R3.P$1 (1), R33.P$1 (1); also elsewhere on the board
SERVO_8/I2C1_SDA: LT_I2C2.4 (SDA1), R6.P$1 (1), R34.P$1 (1); also elsewhere on the board
UART1_RX: CON_UART1.4; also elsewhere on the board
UART1_TX: CON_UART1.3; also elsewhere on the board
UART2_RX: CON_UART2.4; also elsewhere on the board
UART2_TX: CON_UART2.3; also elsewhere on the board
UART3_RX: CON_UART3/5.3; also elsewhere on the board
UART5_RX: CON_UART3/5.6; also elsewhere on the board
USB_DETECT: R12.P$2 (2), R13.P$1 (1); also elsewhere on the board
USB_DISC: Q2.1 (B); also elsewhere on the board
USB_DM: R1.P$2 (2); also elsewhere on the board
USB_DP: R2.P$2 (2), R14.P$1 (1); also elsewhere on the board
USB_VBUS: CON_USB.PIN_1 (1), D3.A, R12.P$1 (1)
VREF: U1.5 (VREF)
V_BAT: CON_CAN/I2C1.2, R11.P$2 (2), R17.P$1 (1)
V_BAT_MEAS: R17.P$2 (2), R18.P$1 (1); also elsewhere on the board
V_IN: CON_CAN/I2C1.3, D3.C, R11.P$1 (1), R20.P$1 (1), R22.P$1 (1), R23.P$2 (2); also elsewhere on the board

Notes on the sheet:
SPI
I2C2
ANALOG1
ANALOG2
GPIO1
UART1
UART2
RC RX\
CAN/I2C1
I2C1_LEVEL_SHIFTER
CAN_TRANSCIEVER
LEDS
USB
JTAG
FIXME
Add connector for no aspirin
fixed via aspirin-connector dummy bd
JP2
JP5
JP4
JP6
JP7
License: CC-BY-SA 3.0
http://creativecommons.org/licenses/by-sa/3.0
(C) 2010-2011 Piotr Esden-Tempski <piotr@esden.net>
(C) 2010-2011 Antoine Drouin <poinix@gmail.com>
(C) 2011 Richard Hatano <rhatano@jobyenergy.com>
(C) 2011 Joby Robotics <info@jobyrobotics.com>
